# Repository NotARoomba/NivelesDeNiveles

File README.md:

<div align="center">
  <br>
  
  <br>
  <h1>🌊Niveles De Niveles🌊</h1>
</div>

<h4 align="center">An early warning application made with <a href="https://reactnative.dev/" target="_blank">React Native</a>.</h4>

<div align="center">

</div>

<p align="center">
  <a href="#key-features">Key Features</a> •
  <a href="https://nivelesdeniveles.org">Website</a> •
  <a href="#how-to-use">How To Use</a> •
  <a href="#download">Download</a> •
  <a href="#credits">Credits</a> •
  <a href="#related">Related</a> •
  <a href="#license">License</a>
</p>
<!-- <div align="center">

</div> -->

## Key Features

- Fast login
- Live updates
- Ability to report disasters
- Use of AI to verify reports

## How To Use

To clone and run this application, you'll need [Git](https://git-scm.com) and [Node.js](https://nodejs.org/en/download/) (which comes with [npm](http://npmjs.com)) installed on your computer. From your command line:

```bash
# Clone this repository
$ git clone https://github.com/NotARoomba/NivelesDeNiveles

# Go into the repository
$ cd NivelesDeNiveles

# Install dependencies
$ npm install

# Run the app
$ npm start
```

## Download
Check out the [website](https://nivelesdeniveles.org) for links.

## Credits

This software uses the following open source packages:

- [React Native](https://reactnative.dev/)
- [Node.js](https://nodejs.org/)
- [NativeWind - TailwindCSS for React Native](https://www.nativewind.dev/)
- [Socket.io](https://socket.io/)

## You may also like...

- [Gravity Simulation](https://github.com/NotARoomba/Gravity-Simulation) - A gravity simulator for web
- [Asteroids](https://github.com/NotARoomba/Asteroids) - A clone of asteroids ported to web from C++

## License

MIT

---

> Website [notaroomba.dev](https://notaroomba.dev) &nbsp;&middot;&nbsp;
> GitHub [@NotARoomba](https://github.com/NotARoomba) &nbsp;&middot;&nbsp;

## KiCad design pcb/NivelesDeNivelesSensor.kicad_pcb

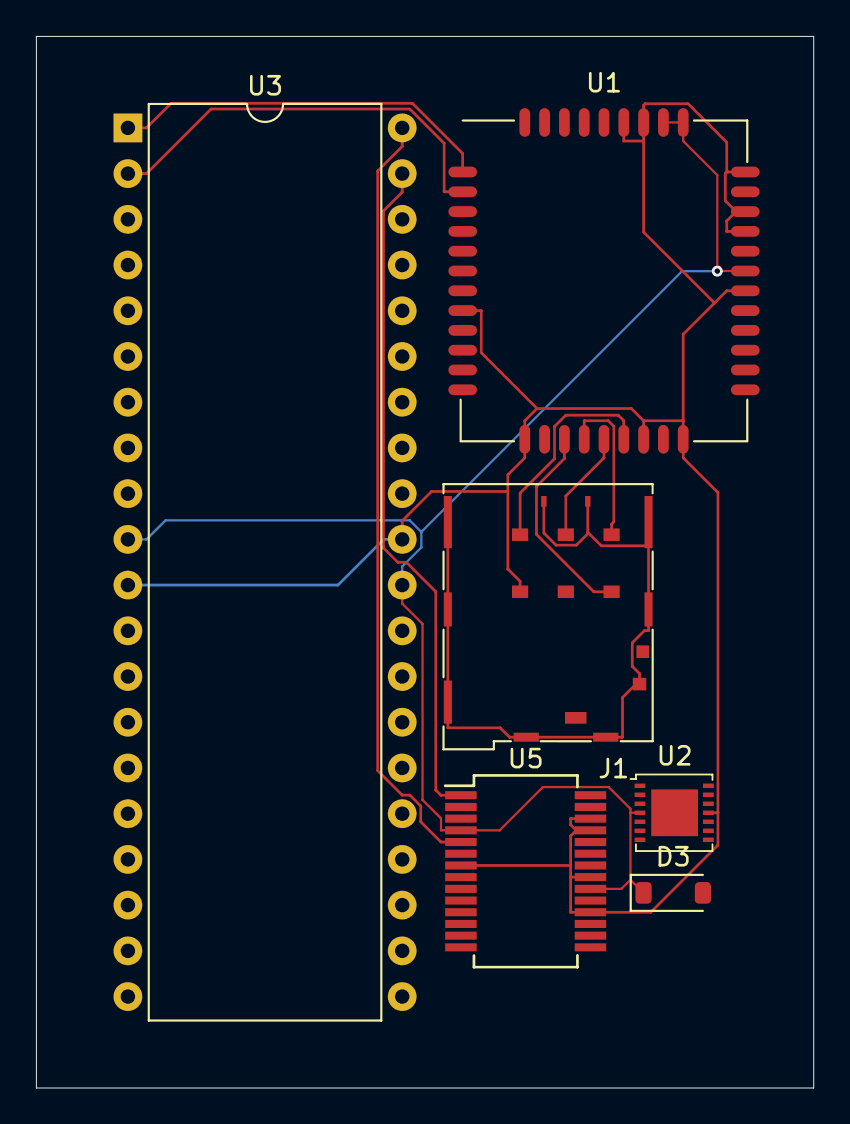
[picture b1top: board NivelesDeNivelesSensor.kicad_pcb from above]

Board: 2 copper layers, 43.2 x 58.4 mm, 6 parts (0 on the bottom side), 10 nets.

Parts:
D3: MBR0520LT; D_SOD-123
J1: JAE_SIM_Card_SF72S006
U1: SIM800C; SIMCom_SIM800C
U2: LP3947; WSON-14-1EP_4.0x4.0mm_P0.5mm_EP2.6x2.6mm
U3: ATmega32L-8P; DIP-40_W15.24mm
U5: FT232RL; SSOP-28_5.3x10.2mm_P0.65mm

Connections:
+5V: D3.1 (K), U1.28 (VRTC), U1.34 (VBAT), U1.35 (VBAT), U2.4 (BATT), U3.10 (VCC), U3.30 (AVCC), U5.4 (VCCIO), U5.20 (VCC)
/C1: J1.C1 (VCC), U1.18 (SIM_VDD)
/C2: J1.C2 (RST), U1.17 (SIM_RST)
/C3: J1.C3 (CLK), U1.16 (SIM_CLK)
/C6: J1.C7 (I/O), U1.15 (SIM_DATA)
GND: J1.C5 (GND), U1.8 (GND), U1.13 (GND), U1.19 (GND), U1.21 (GND), U1.27 (GND), U1.30 (GND), U1.31 (GND), U1.33 (GND), U1.36 (GND), U1.37 (GND), U2.11 (GND), U3.11 (GND), U3.31 (GND), U5.7 (GND), U5.18 (GND), U5.21 (GND), U5.25 (AGND), U5.26 (TEST)
unnamed: U1.2 (UART1_RXD), U3.2 (PB1)
unnamed: U1.1 (UART1_TXD), U3.1 (PB0)
unnamed: U3.40 (PA0), U5.5 (RXD)
unnamed: U3.39 (PA1), U5.1 (TXD)

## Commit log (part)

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2023-09-27 test acknowledgement
2023-09-27 location data done
2023-09-27 log user
2023-09-27 finished sensors and stuff
2023-09-27 pruning data after 2 hours of inactivity
    also improved the range of the checks for getting the incidents near their range and not any less
2023-09-27 added gif and correct variables
2023-09-27 fix backend
2023-09-27 database agregation learning
2023-09-27 remove sensors from agregate
2023-09-27 geonear
2023-09-27 coordinates
2023-09-27 geowithin
2023-09-27 revert range optimizations
2023-09-27 camera and stuff
2023-09-28 need to make maps work on load
2023-09-28 ignset
2023-09-28 use axios
2023-09-28 incidents and sensors
2023-09-28 console log user
2023-09-28 added markers
2023-09-28 prettier and finished with markers and incidents
2023-09-29 location is null
2023-09-29 check fro reports and camera done
2023-09-29 router and res
2023-09-29 req testing
2023-09-29 500 mb limit
2023-09-29 changed api
2023-09-30 whoops
2023-09-30 use atomic operators
2023-09-30 set level too
2023-10-01 update range and level without fullDocument
2023-10-01 user null
2023-10-01 return and callback
2023-10-01 run prune on start
2023-10-01 atomic operators
2023-10-01 logging user
2023-10-01 log error
2023-10-01 change min interval
2023-10-01 cleanup and bug fixes
2023-10-01 finally implemented range checks in meters
2023-10-01 prettier
2023-10-03 dstuff
2023-10-04 node modules
2023-10-05 updatejson
2023-10-06 name for backend and remove hmac for easy access
2023-10-07 add back hmac and server
2023-10-07 need to work on y server
2023-10-08 test without hmac
2023-10-08 insert and remove hmac
2023-10-08 remove insert
2023-10-08 add pipeline and changestream
2023-10-08 add back hmac
2023-10-08 hmac finally working
2023-10-08 test
2023-10-08 forgot signs
2023-10-09 going to rename
2023-10-09 spanish
2023-10-09 corrección
2023-10-09 no sensors?
2023-10-09 over whoops
2023-10-09 remove logging
2023-10-09 change range of incident and stuff
2023-10-09 sadas
2023-10-09 remove location for sensors
2023-10-09 change to one to see changes in state
2023-10-10 change incident
2023-10-13 testing
2023-10-26 push to app store (in progress)
2023-10-28 start of localization
2023-10-29 added english localization
2023-10-29 finished adding localizations
2023-10-29 fixed reports
2023-10-30 add loading spinning
2023-10-30 loading screen
2023-10-30 Revert xcproj
    This reverts commit bd48396f6803a1eecc5c10df18ed9ed6ec0b42b2.
2023-10-30 change version
2023-10-30 added logout and better spinner
2023-10-31 Update Localizations.tsx
    fn and en
2023-10-31 Update Localizations.tsx
    checked
2023-10-31 Update Localizations.tsx
    double check
2023-10-31 5/12 width
2023-10-31 try catch for generic error
2023-10-31 start of chinese and spanish default
2023-10-31 Create CNAME
2023-11-01 added half of website
2023-11-01 finalize vendor
2023-11-01 chinese localizations
2023-11-01 misc fixes
2023-11-01 added more descriptive sensors
2023-11-01 start of react webpage
2023-11-02 added some stuffs still have to finish bottom
2023-11-02 update server
2023-11-02 forgot user
2023-11-02 console.log dist
2023-11-02 fix merge range and v2.4.0
2023-11-02 privacy policy
2023-11-02 move pdf
2023-11-02 change name
2023-11-03 prettier and 2.4 android
2023-11-03 apk and aab
2023-11-04 Update Localizations.tsx
    changed zona de () str
2023-11-04 changed icon and also pushed to google play
2023-11-04 notification service and testing backend
2023-11-04 headings
2023-11-04 onesignal send notification
2023-11-04 log incidents
2023-11-04 onesignal
2023-11-04 update level test and prettier
2023-11-04 add localizations to notification
2023-11-04 fix bugs with text box not appearing
2023-11-04 version 2.5
2023-11-04 stuff
2023-11-04 html version of policy
2023-11-04 TEMPORARY BE SURE TO REVERT
2023-11-04 REVERT THIS
2023-11-04 add some support for spanish stuffs
2023-11-05 opt out broken
2023-11-05 fix login with notifications and notifications when in safe zone (hopefully)
2023-11-05 beforechange required
2023-11-05 try to create the collection
2023-11-05 dislike math
2023-11-05 release aab and apk
2023-11-05 error sending code fixed
2023-11-05 FORGOT NEW API IN ANDROID
2023-11-05 FOTGOT API URL
2023-11-05 test?
2023-11-05 change radius to 20
2023-11-05 logs
2023-11-05 added a modal to request notifications
2023-11-05 modal
2023-11-06 Version 2.6!
    Added permission modals for location and notifications
2023-11-06 light background for text box
2023-11-06 more coherent looks
2023-11-06 2.5.3 rollback for proper versioning
2023-11-06 apk to make dislcosure vid
2023-11-06 stuff test
2023-11-06 precise location and background location done
2023-11-07 fixed bug with multiple users in the lcoation range
2023-11-07 add updade evey 5 minutes and prettier
2023-11-07 2.5.4 ios
2023-11-07 number not exist
2023-11-08 upgrade dependencies and backgroudn updating
2023-11-11 bump version and remove extra dependencies
2023-11-11 prettier and remove console logs
2023-11-11 android 2.5.6
2023-11-12 adding more stuff
2023-11-12 v2.5.7
    fix for watch location not updating on button click
2023-11-12 2.5.7 and updated website
2023-11-12 new website done in react
2023-11-12 add 404 page
2023-11-13 add app banner
2023-11-13 prettier and add mobile stuffs
2023-11-13 styled app banner
2023-11-13 relative path
2023-11-13 change some things
2023-11-14 index html not redirecting on error
2023-11-15 external id
2023-11-15 supposed fix
2023-11-16 push and stuff
2023-11-17 lower range
2023-11-17 logging
2023-11-17 users in zone to peevntdouble firing
2023-11-17 more checks
2023-11-17 fixed bugs and v2.5.8
2023-11-17 remove websocket interval
2023-11-17 add motion usage permission and localizations
2023-11-17 test logging
2023-11-18 fix multiple websockets and location done
2023-11-18 function and refactor also added moving into a danger zone
2023-11-18 android build stuff
2023-11-18 stuff and android release
2023-11-20 fixes to bg location on android
2023-11-20 finsihed build
2023-11-23 arduino stuff and database logs
2023-11-24 advice router
2023-11-24 added other geolocation
2023-11-24 Revert "added other geolocation"
    This reverts commit 10bfd0fcdc14fc1757748fe88a2474883ec0d1ff.
2023-11-25 added stuff
2023-11-25 stuffs
2023-11-25 stuf
2023-11-25 more info text español
2023-11-25 eng y esp
    done
2023-11-25 newline
2023-11-25 localizations moremore info done
2023-11-25 website localization clases
    e
2023-11-25 e
    e
2023-11-25 Localizacion español pagina web done
    eee
2023-11-26 localizations done
2023-11-26 minor fixes and done
2023-11-26 change version and F
2023-11-26 new apk
2023-11-26 need to get coarse location first on android
2023-11-26 added localizations to website
2023-11-26 localizations
2023-11-26 prettier and added multiple reports
2023-11-26 added avalanche detection
2023-11-27 danger level safe bug fix
2023-11-27 bug fixes
2023-11-27 website
    eawsfa
2023-11-27 website
    efwasfewa
2023-11-27 websireAHAHH
    rfesd
2024-02-28 pcb starter
2024-03-12 pcb updates
2024-10-07 add stuff
2024-10-07 small updates
2024-10-20 updated profile
2024-10-31 update react native
2024-11-03 migrate to rust start
2024-11-03 port
2024-11-03 port type casting
2024-11-03 change to axum
2024-11-03 rocket start
2024-11-03 users router done
2024-11-03 updated api
2024-11-03 add openssl
2024-11-04 add verify route
2024-11-04 finished static routes
2024-11-06 added websockets
2024-11-06 openssl
2024-11-06 old prettier and finally finish backend
2024-11-06 added checks for indexes
2024-11-06 try with other json
2024-11-06 serialize to u8
2024-11-06 convert all to json for compatibility
2024-11-06 remove old js
2024-11-06 need to use path whoops
2024-11-06 add post
2024-11-06 update paths and fix report
2024-11-07 update paths
2024-11-07 finally fix pathing
2024-11-07 info to debug
2024-11-07 into and report types
2024-11-07 cleanup
2024-11-07 pipeline and update stuff
2024-11-07 add concurency
2025-01-25 Update CNAME
